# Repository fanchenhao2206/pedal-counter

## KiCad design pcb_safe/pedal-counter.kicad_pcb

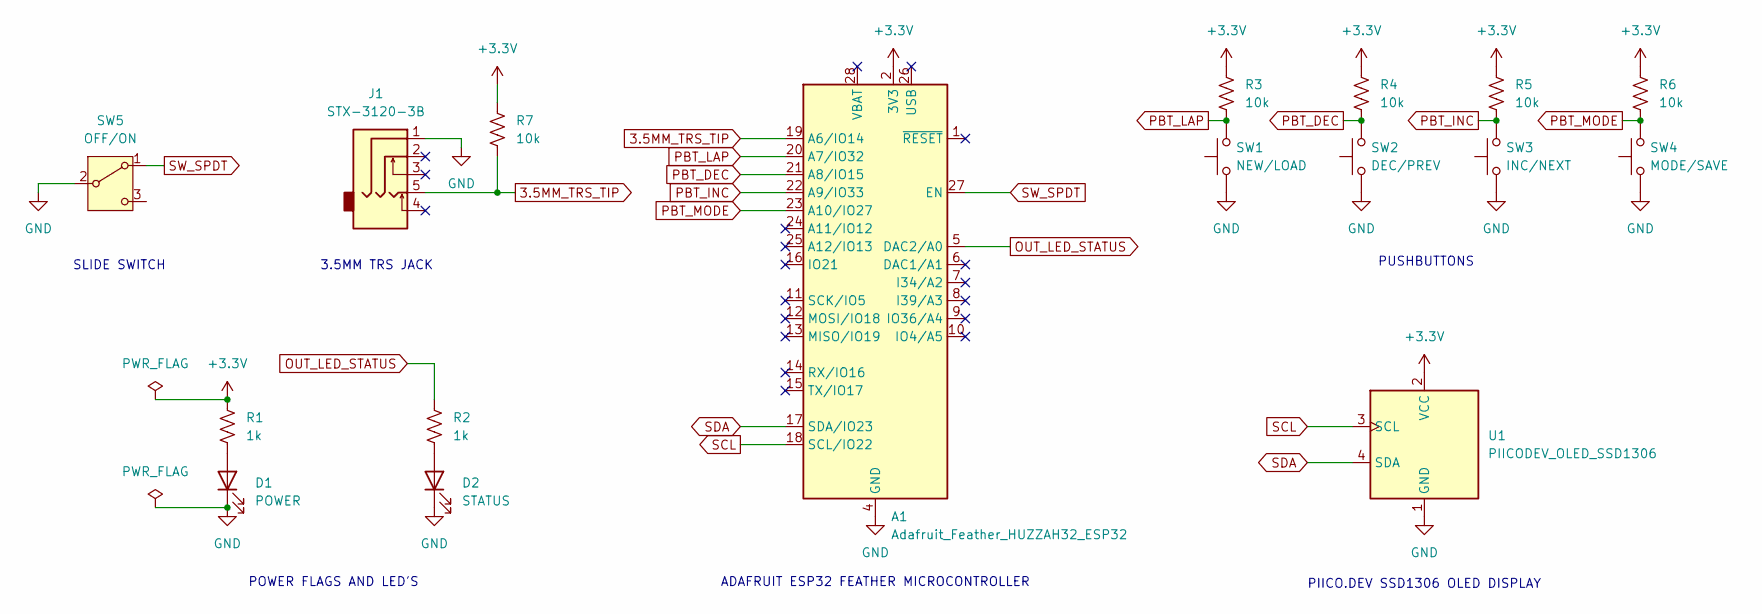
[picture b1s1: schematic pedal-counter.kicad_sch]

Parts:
A1: Adafruit_Feather_HUZZAH32_ESP32; Adafruit_Feather
D1: POWER; LED_D5.0mm
D2: STATUS; LED_D5.0mm
J1: STX-3120-3B
R1, R2: 1k; R_Axial_DIN0207_L6.3mm_D2.5mm_P10.16mm_Horizontal
R3, R4, R5, R6, R7: 10k; R_Axial_DIN0207_L6.3mm_D2.5mm_P10.16mm_Horizontal
SW1: NEW/LOAD; SW_PUSH_6mm
SW2: DEC/PREV; SW_PUSH_6mm
SW3: INC/NEXT; SW_PUSH_6mm
SW4: MODE/SAVE; SW_PUSH_6mm
SW5: OFF/ON; CUSTOM_SW_SLIDE_SPDT
U1: PIICODEV_OLED_SSD1306

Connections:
3.5MM_TRS_TIP: A1.19 (A6/IO14), J1.5, R7.2
+3.3V: A1.2 (3V3), R1.1, R3.1, R4.1, R5.1, R6.1, R7.1, U1.2 (VCC)
GND: A1.4 (GND), D1.1 (K), D2.1 (K), J1.1, SW1.1, SW2.1, SW3.1, SW4.1, SW5.2 (B), U1.1 (GND)
unnamed: D1.2 (A), R1.2
unnamed: D2.2 (A), R2.2
OUT_LED_STATUS: A1.5 (DAC2/A0), R2.1
PBT_DEC: A1.21 (A8/IO15), R4.2, SW2.2
PBT_INC: A1.22 (A9/IO33), R5.2, SW3.2
PBT_LAP: A1.20 (A7/IO32), R3.2, SW1.2
PBT_MODE: A1.23 (A10/IO27), R6.2, SW4.2
SCL: A1.18 (SCL/IO22), U1.3 (SCL)
SDA: A1.17 (SDA/IO23), U1.4 (SDA)
SW_SPDT: A1.27 (EN), SW5.1 (A)

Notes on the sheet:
POWER FLAGS AND LED'S
ADAFRUIT ESP32 FEATHER MICROCONTROLLER
3.5MM TRS JACK
SLIDE SWITCH
PIICO.DEV SSD1306 OLED DISPLAY
PUSHBUTTONS

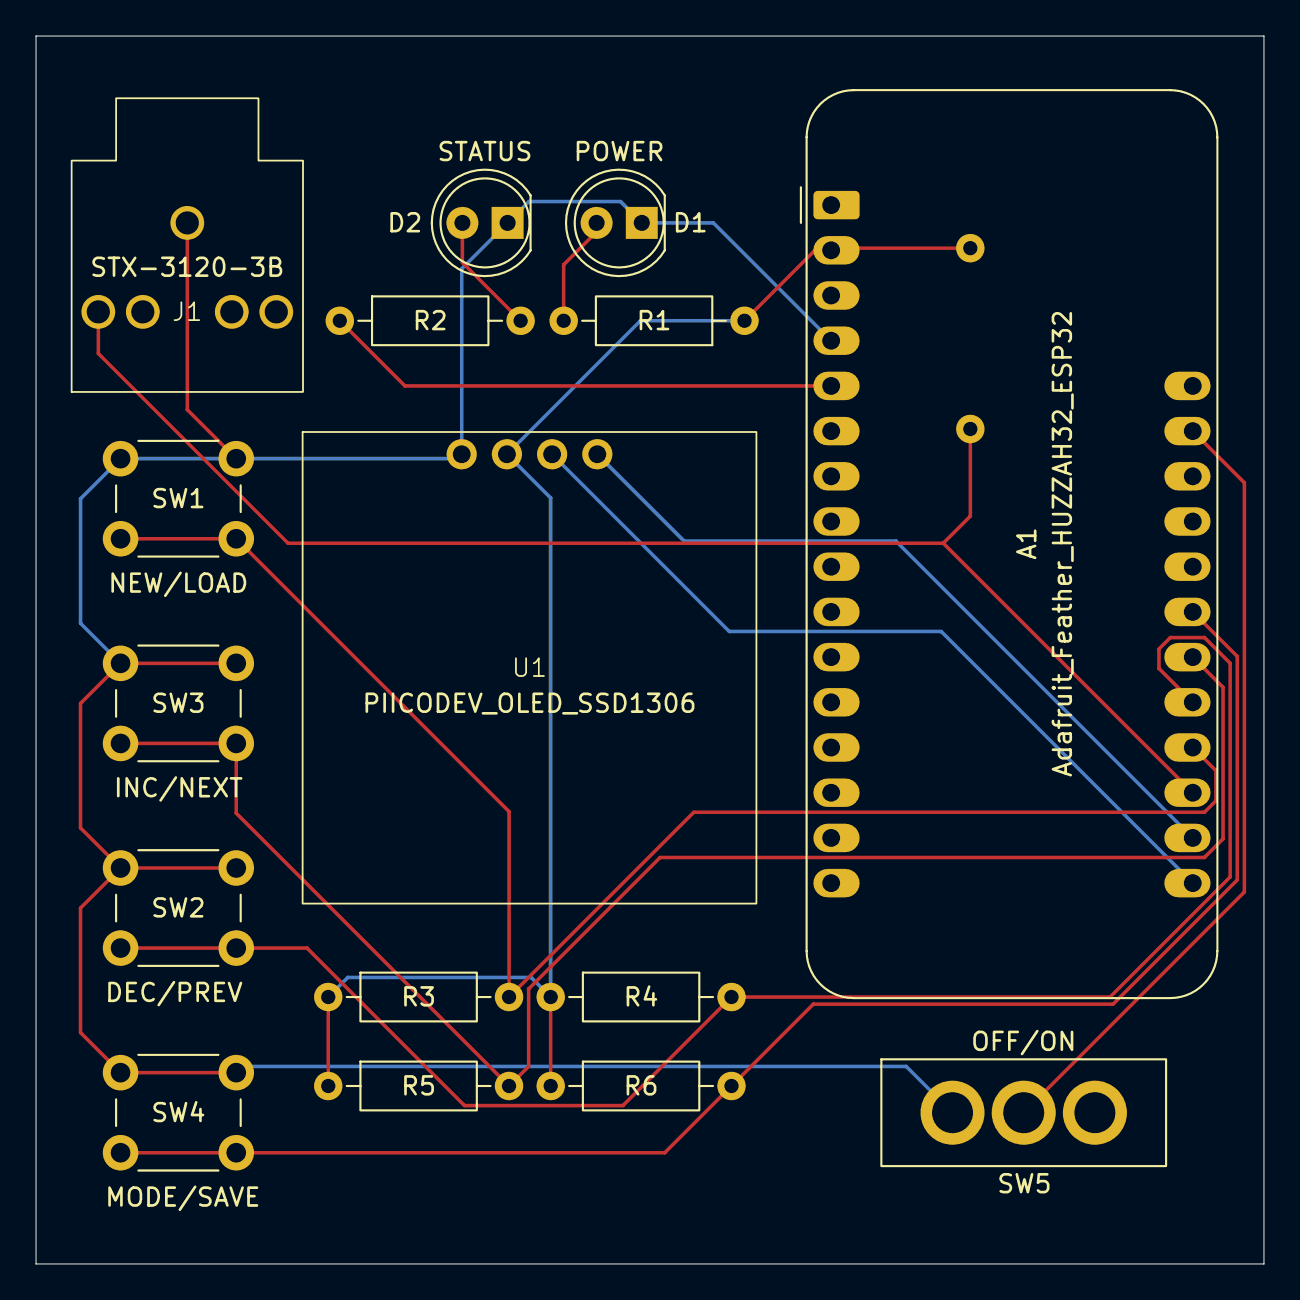
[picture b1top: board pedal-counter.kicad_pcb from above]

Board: 2 copper layers, 69.0 x 69.0 mm, 17 parts (1 on the bottom side), 13 nets.
